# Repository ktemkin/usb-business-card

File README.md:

# Work-in-progress: inexpensive USB target for workshops

This is a work in progress. :)

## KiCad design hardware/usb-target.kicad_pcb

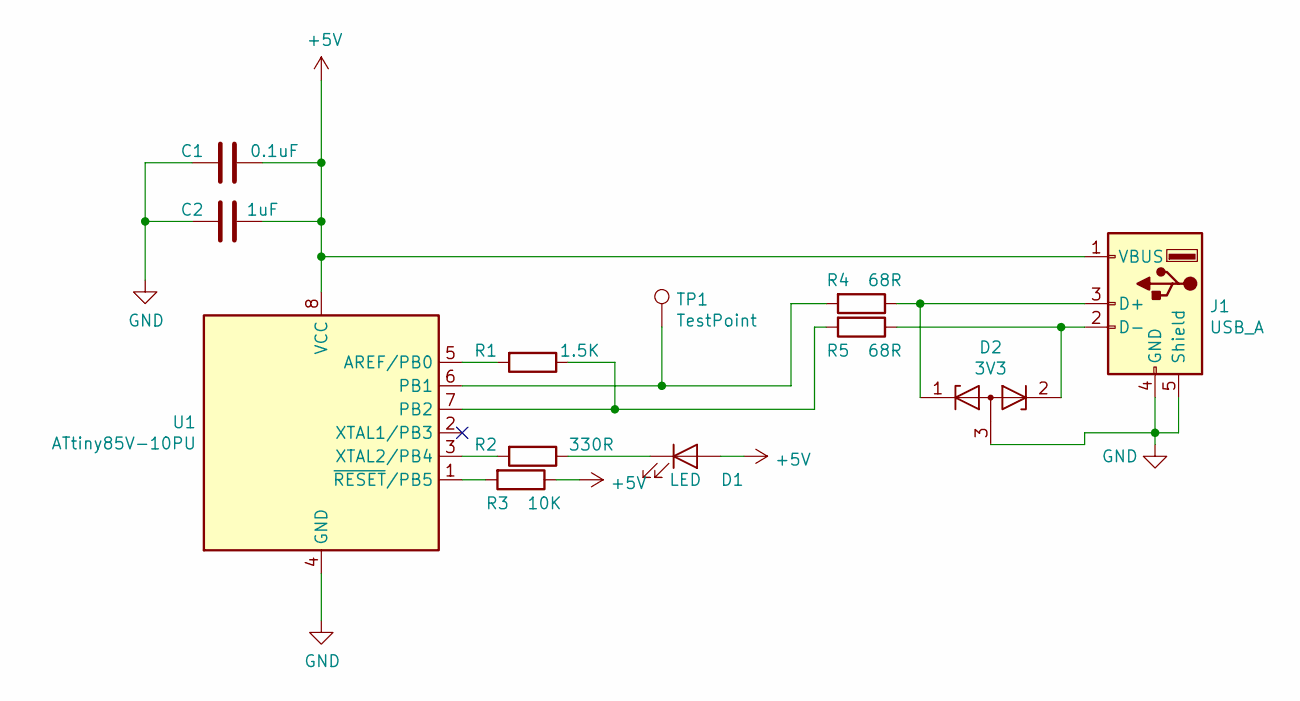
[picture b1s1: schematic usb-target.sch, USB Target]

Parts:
C1: 0.1uF; R_0805_2012Metric
C2: 1uF; R_0805_2012Metric
D1: LED; R_0805_2012Metric
D2: 3V3; SOT-23
J1: USB_A; usb_A_pcb
R1: 1.5K; R_0805_2012Metric
R2: 330R; R_0805_2012Metric
R3: 10K; R_0805_2012Metric
R4, R5: 68R; R_0805_2012Metric
TP1: TestPoint; TestPoint_Pad_D2.0mm
U1: ATtiny85V-10PU; SOIC-8_5.23x5.23mm_P1.27mm

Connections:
+5V: C1.2, C2.2, D1.2 (A), J1.1 (VBUS), R3.1, U1.8 (VCC)
GND: C1.1, C2.1, D2.3 (A), J1.4 (GND), J1.5 (Shield), U1.4 (GND)
unnamed: D1.1 (K), R2.1
unnamed: D2.1 (K), J1.3 (D+), R4.1
unnamed: D2.2 (K), J1.2 (D-), R5.1
unnamed: R1.1, R5.2, U1.7 (PB2)
unnamed: R1.2, U1.5 (AREF/PB0)
unnamed: R2.2, U1.3 (XTAL2/PB4)
unnamed: R3.2, U1.1 (~RESET~/PB5)
unnamed: R4.2, TP1.1, U1.6 (PB1)

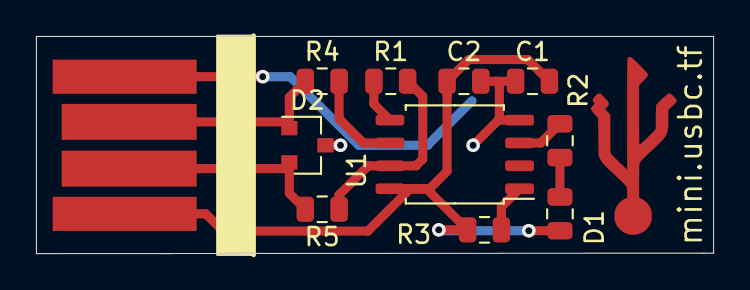
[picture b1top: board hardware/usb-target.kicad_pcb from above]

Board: 2 copper layers, 37.6 x 12.1 mm, 12 parts (0 on the bottom side), 10 nets.

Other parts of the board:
LOGO0: LOGO; usb_tools_logo

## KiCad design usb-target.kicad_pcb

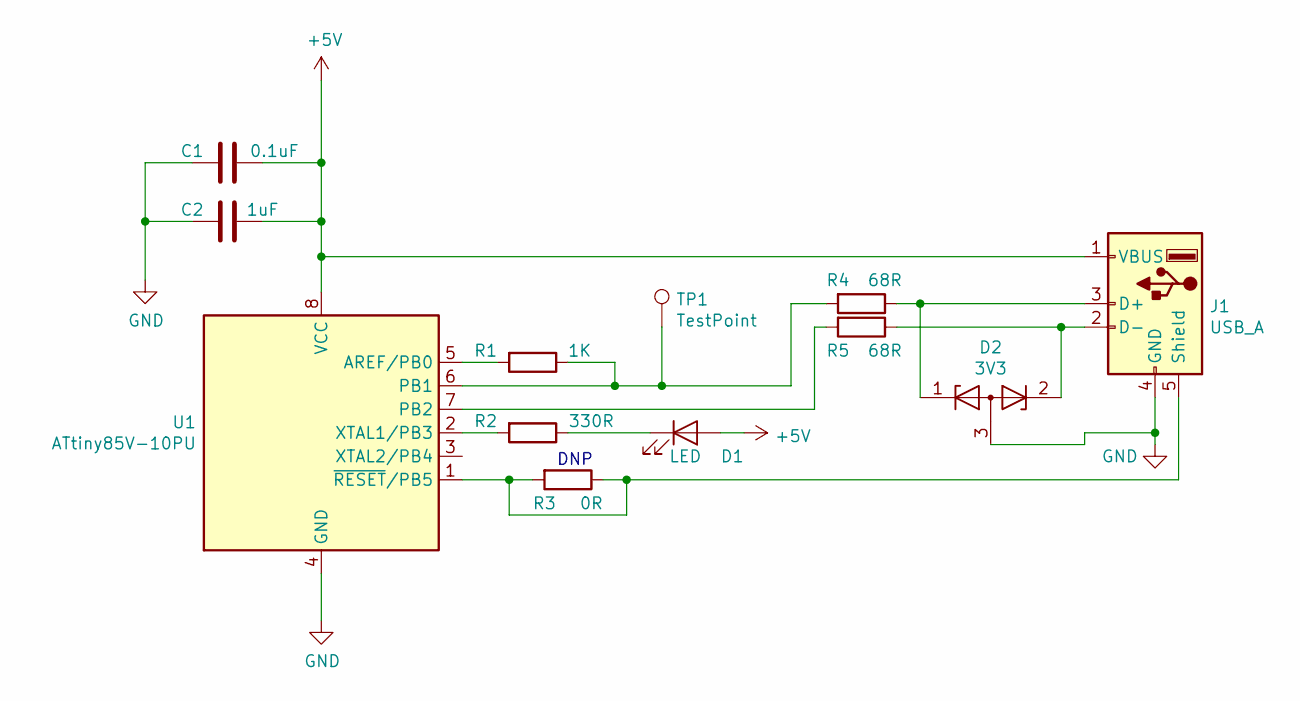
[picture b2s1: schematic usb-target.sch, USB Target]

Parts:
C1: 0.1uF; R_0805_2012Metric
C2: 1uF; R_0805_2012Metric
D1: LED; R_0805_2012Metric
D2: 3V3; SOT-23
J1: USB_A; usb_A_pcb
R1: 1K; R_0805_2012Metric
R2: 330R; R_0805_2012Metric
R3: 0R; R_0805_2012Metric
R4, R5: 68R; R_0805_2012Metric
TP1: TestPoint; TestPoint_Pad_D2.0mm
U1: ATtiny85V-10PU; SOIC-8_3.9x4.9mm_P1.27mm

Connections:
+5V: C1.2, C2.2, D1.2 (A), J1.1 (VBUS), U1.8 (VCC)
GND: C1.1, C2.1, D2.3 (A), J1.4 (GND), U1.4 (GND)
unnamed: D1.1 (K), R2.1
unnamed: D2.1 (K), J1.3 (D+), R4.1
unnamed: D2.2 (K), J1.2 (D-), R5.1
unnamed: J1.5 (Shield), R3.1, R3.2, U1.1 (~RESET~/PB5)
unnamed: R1.1, R4.2, TP1.1, U1.6 (PB1)
unnamed: R1.2, U1.5 (AREF/PB0)
unnamed: R2.2, U1.2 (XTAL1/PB3)
unnamed: R5.2, U1.7 (PB2)

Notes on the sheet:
DNP

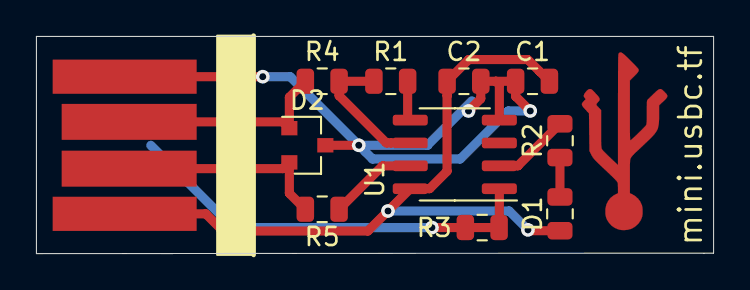
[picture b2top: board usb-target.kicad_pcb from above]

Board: 2 copper layers, 37.6 x 12.1 mm, 11 parts (0 on the bottom side), 10 nets.

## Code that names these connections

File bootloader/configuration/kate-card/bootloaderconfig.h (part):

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 * 
 * Controller type: ATtiny 85 - 16.5 MHz
 * Configuration:   Default configuration
 *       USB D-     :   PB2
 *       USB D+     :   PB1
 *       USB Pull R :
 *       Entry      :   Always
 *       LED        :   PB4, active low
 *       OSCCAL     :   Stays at 16 MHz
 * Note: Uses 16.5 MHz V-USB implementation with PLL
 * Last Change:     Mar 16,2014
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 *                      external jumper. 
 *                      Adds 34 bytes.
 *
 *       JUMPER_PIN     Pin the jumper is connected to. (e.g. PB0)
 *       JUMPER_PORT    Port out register for the jumper (e.g. PORTB)  
 *       JUMPER_DDR     Port data direction register for the jumper (e.g. DDRB)  
 *       JUMPER_INP     Port inout register for the jumper (e.g. PINB)  
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
#define ENTRYMODE ENTRY_ALWAYS

#define JUMPER_PIN    PB0
#define JUMPER_PORT   PORTB 
#define JUMPER_DDR    DDRB 
#define JUMPER_INP    PINB 
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
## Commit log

2019-10-11 initial commit: initial, untested design
2019-10-20 add bootloader to repostiory
2019-10-20 bootloader & hardware: update to (hopefully) production version
2019-10-29 bootloader: update configuration to match final board settings
2019-10-29 hardware: update component value to match v-usb recommendations

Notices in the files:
bootloader/configuration/kate-card/bootloaderconfig.h:
License: GNU GPL v2 (see License.txt
hardware/usb-target.sch:
licensed under the CERN OHL 1.2
